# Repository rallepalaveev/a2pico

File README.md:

# A2Pico Reference Hardware

This repository is the home of the A2Pico reference hardware. Please refer to the upstream repository at https://github.com/oliverschmidt/a2pico for general information on A2Pico.

## Hardware Revision History

Version 1.4 is the innitial design with 3x 74LVC245 and 1x 74HC08 to prove the concept. However it is obsolete as it does not switch off the Expansion ROM ($C800-$CFFF), which is always available and could cause data bus conlisions if used with other cards that use this memory space.

Version 1.5 switches off the Expansion ROM ($C800-$CFFF) when $CFFF is accessed or when reset is issued, and switches it back on again when the slot memory is accessed (IOSelect).

Version 1.6 combines 3 of the logic chips into a PLD. 74LS08, 74LS133 and 74LS02 are replaced by ATF22V10.

The RPI usage is as follows:

| GPIO    | Usage     |
|:--------|:----------|
| 0       |  UART TX  |
| 1       |  UART RX  |
| 2 - 13  | A0 - A11  |
| 14      | R/W       |
| 15 - 22 | D0 - D7   |
| 26      | ENBL      |
| 27      | IRQ       |
| 28      | RES       |

Version "n" has support for a MicroSD card with **no** ExtROM capability.

The RPI usage of the "n" versions is as follows:

| GPIO    | Usage     |
|:--------|:----------|
| 0       |  SPI RX   |
| 1       |  SPI CSn  |
| 2       |  SPI SCK  |
| 3       |  SPI TX   |
| 4       |  NMI      |
| 5 - 12  | A0 - A7   |
| 13      | DEVSEL    |
| 14      | R/W       |
| 15 - 22 | D0 - D7   |
| 26      | ENBL      |
| 27      |  IRQ      |
| 28      |  RES      |

Version 1.7 is a direct successor of v1.4. Changes are replacing the 7408 by a 7411, data direction is controlled now by the Raspberry Pi Pico, which allows for all memory locations to be emulated, ENBL has an option to be is driven by a voltage divider for minimum latency, a USB "back power" option is included.

The RPI usage is as follows:

| GPIO    | Usage     |
|:--------|:----------|
| 0       |  UART TX  |
| 1       |  DATA dir |
| 2 - 13  | A0 - A11  |
| 14      | R/W       |
| 15 - 22 | D0 - D7   |
| 26      | ENBL      |
| 27      | IRQ       |
| 28      | RES       |

Versions 2.4 and 2.5 are a new hardware variant of v1.7 - TH and SMD respectively. The major change is that A0-7 and D0-7 are multiplexed and an SD card interface is added.
The RPI usage is as follows:

| GPIO    | Usage     |
|:--------|:----------|
| 0       |  UART Tx  |
| 1       |  UART Rx  |
| 2       |  ENBL     |
| 3 - 10  | AD0 - AD7 |
| 11 - 14 | A8 - A11  |
| 15      | R/W       |
| 16      | PHI1      |
| 17      | RES       |
| 18      | IRQ       |
| 19      | CMD       |
| 20      | DAT0      |
| 21      | DAT3      |
| 22      | CLK       |
| 26      | AL-OE     |
| 27      | D-OE      |
| 28      | DDIR      |

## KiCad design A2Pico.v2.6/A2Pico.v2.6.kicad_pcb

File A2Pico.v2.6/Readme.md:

A2Pico Version 2.6 is a follow-up of 2.4 with some small changes - changed form factor, added USB power slide switch, added USB power LED.

The RPI usage is as follows:

| GPIO    | Usage     |
|:--------|:----------|
| 0       |  UART Tx  |
| 1       |  UART Rx  |
| 2       |  ENBL     |
| 3 - 10  | AD0 - AD7 |
| 11 - 14 | A8 - A11  |
| 15      | R/W       |
| 16      | Ф1        |
| 17      | RES       |
| 18      | IRQ       |
| 19      | CMD       |
| 20      | DAT0      |
| 21      | DAT3      |
| 22      | CLK       |
| 26      | AL-OE     |
| 27      | D-OE      |
| 28      | DDIR      |

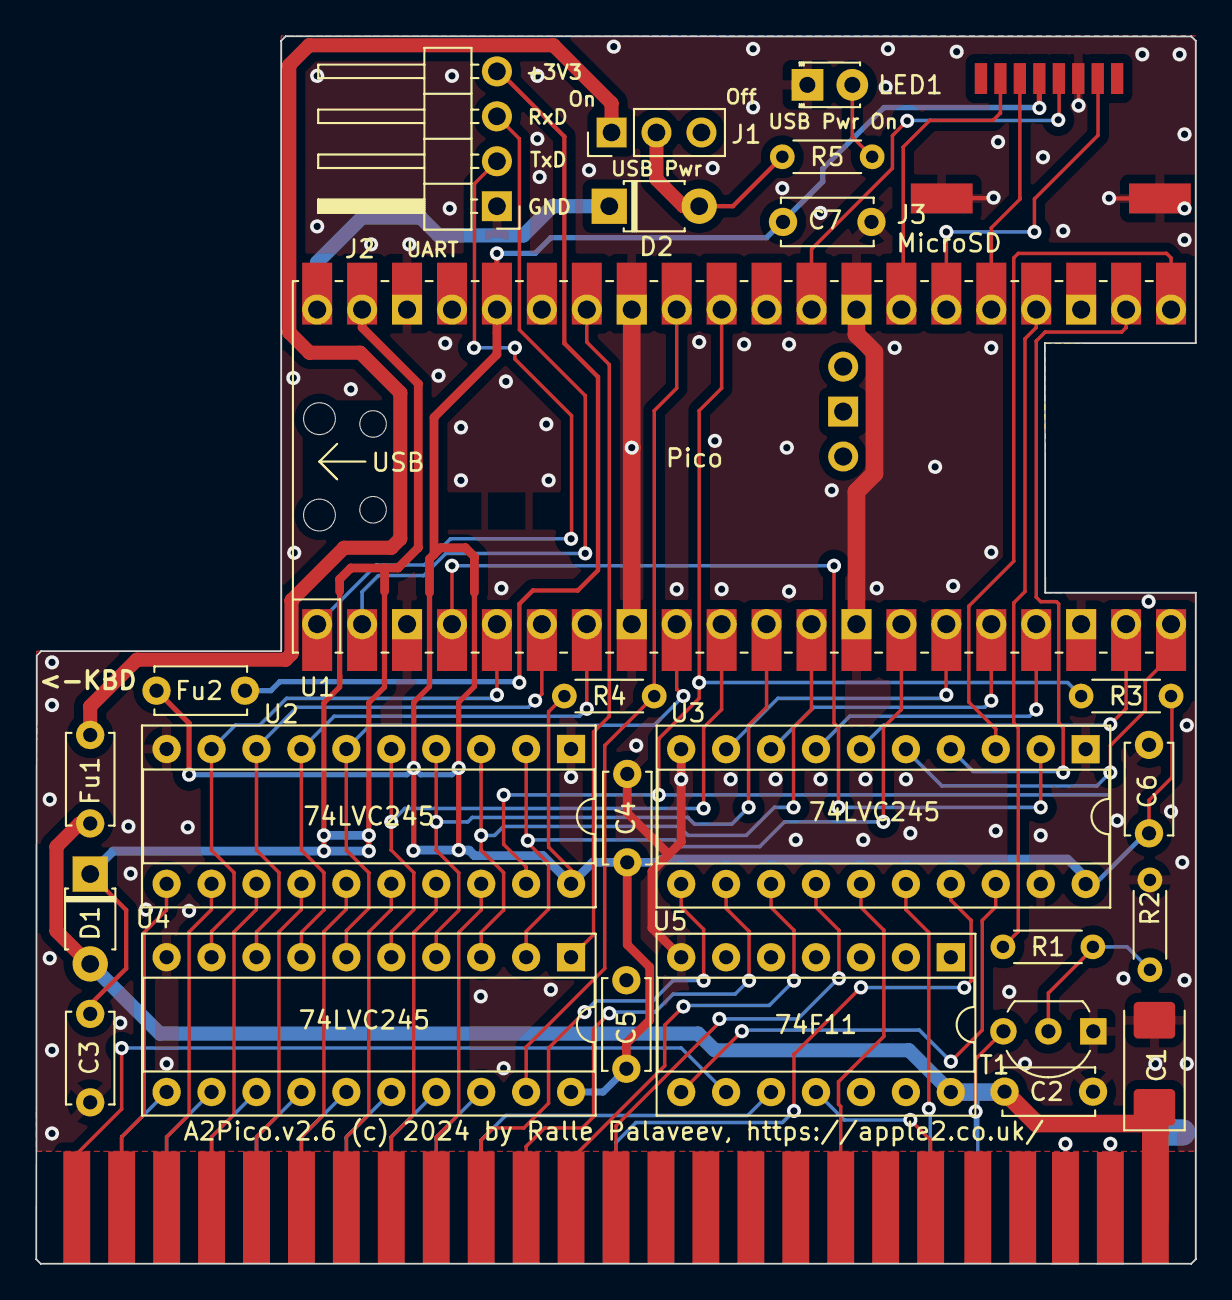
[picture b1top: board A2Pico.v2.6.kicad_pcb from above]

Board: 2 copper layers, 65.5 x 69.4 mm, 25 parts (0 on the bottom side), 31 nets.

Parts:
C1: 220uF; CP_EIA-6032-15_Kemet-U
C2, C3, C4, C5, C6, C7: 100n; C_Disc_D5.0mm_W2.5mm_P5.00mm
D1, D2: D_T-1_P5.08mm_Horizontal
Fu1: 500mA; C_Disc_D5.0mm_W2.5mm_P5.00mm
Fu2: 100mA; C_Disc_D5.0mm_W2.5mm_P5.00mm
J1: PinHeader_1x03_P2.54mm_Vertical
J2: PinHeader_1x04_P2.54mm_Horizontal
LED1: LED_D1.8mm_W3.3mm_H2.4mm
R1, R5: 1k; R_Axial_DIN0204_L3.6mm_D1.6mm_P5.08mm_Horizontal
R2, R3, R4: 10k; R_Axial_DIN0204_L3.6mm_D1.6mm_P5.08mm_Horizontal
T1: TO-92L_Inline_Wide
U1: Pico / PicoW; RPi_PicoW_SMD_TH
U2, U3, U4: 74LVC245; DIP-20_W7.62mm_Socket
U5: 74F11; DIP-14_W7.62mm_Socket

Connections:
3.3V: C4.1, C5.1, C6.1, C7.1, Fu2.1, R3.1, R4.2, U1.36 (3V3), U2.20, U3.20, U4.20
3.3V_out: Fu2.2, J2.4
5V: C1.1, C2.2, D1.2, Fu1.1, U5.14
AL-OE: R3.2, U1.31 (GPIO26_ADC0), U2.19
D-Dir: U1.34 (GPIO28_ADC2), U4.1
D-OE: R4.1, U1.32 (GPIO27_ADC1), U4.19
ENBL: U3.18, U5.8
GND: C1.2, C2.1, C3.1, C4.2, C5.2, C6.2, C7.2, J2.1, LED1.1, R2.2, T1.1, U1.3 (GND), U1.8 (GND), U1.13 (GND), U1.18 (GND), U1.23 (GND), U1.28 (GND), U1.33 (AGND), U1.38 (GND), U2.1, U2.10, U3.1, U3.10, U3.19, U4.10, U5.7
J1-1: Fu1.2, J1.1
J1-2: D2.2, J1.2, R5.2
L-A8: U1.15 (GPIO11), U3.9
L-A9: U1.16 (GPIO12), U3.8
L-A10: U1.17 (GPIO13), U3.7
L-A11: U1.19 (GPIO14), U3.6
L-AD0: U1.5 (GPIO3), U2.9, U4.9
L-AD1: U1.6 (GPIO4), U2.8, U4.8
L-AD2: U1.7 (GPIO5), U2.7, U4.7
L-AD3: U1.9 (GPIO6), U2.6, U4.6
L-AD4: U1.10 (GPIO7), U2.5, U4.5
L-AD5: U1.11 (GPIO8), U2.4, U4.4
L-AD6: U1.12 (GPIO9), U2.3, U4.3
L-AD7: U1.14 (GPIO10), U2.2, U4.2
L-ENBL: U1.4 (GPIO2), U3.2
L-IRQ: R1.2, U1.24 (GPIO18)
L-PHI1: U1.21 (GPIO16), U3.3
L-RW: U1.20 (GPIO15), U3.5
L-Reset: U1.22 (GPIO17), U3.4
Rx: J2.3, U1.2 (GPIO1)
Tx: J2.2, U1.1 (GPIO0)
VBUS: D2.1, U1.40 (VBUS)
VSYS: C3.2, D1.1, U1.39 (VSYS)

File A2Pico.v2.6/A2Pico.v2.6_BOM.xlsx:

Comment | Designator
10V 100uF | C1
16V 100nF | C2,C3,C4,C5,C6,C7,C8
1K | R1,R5
10K | R2,R3,R4
MicroSD slot without cover, Attend 112K-TAA0-RA1 | J3
Slide switch CUI Devices MSS-102568-14A-90-D | J1
3A Right-Angle Square Pins 2.5mm 4P 6mm | J2
6V 500mA Resettable Fuse | Fu1
6V 100mA Resettable Fuse | Fu2
1N5819 | D1,D2
2N7002 | T1
Raspberry Pi PICO | U1
SN74LVC245N | U2,U3,U4
74F11 | U5
LED | LED1

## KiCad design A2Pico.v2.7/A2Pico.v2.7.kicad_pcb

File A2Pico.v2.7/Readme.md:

A2Pico Version 2.7 is a follow-up of 2.5 with some small changes - changed form factor, added USB power slide switch, added USB power LED.

The RPI usage is as follows:

| GPIO    | Usage     |
|:--------|:----------|
| 0       |  UART Tx  |
| 1       |  UART Rx  |
| 2       |  ENBL     |
| 3 - 10  | AD0 - AD7 |
| 11 - 14 | A8 - A11  |
| 15      | R/W       |
| 16      | Ф1        |
| 17      | RES       |
| 18      | IRQ       |
| 19      | CMD       |
| 20      | DAT0      |
| 21      | DAT3      |
| 22      | CLK       |
| 26      | AL-OE     |
| 27      | D-OE      |
| 28      | DDIR      |

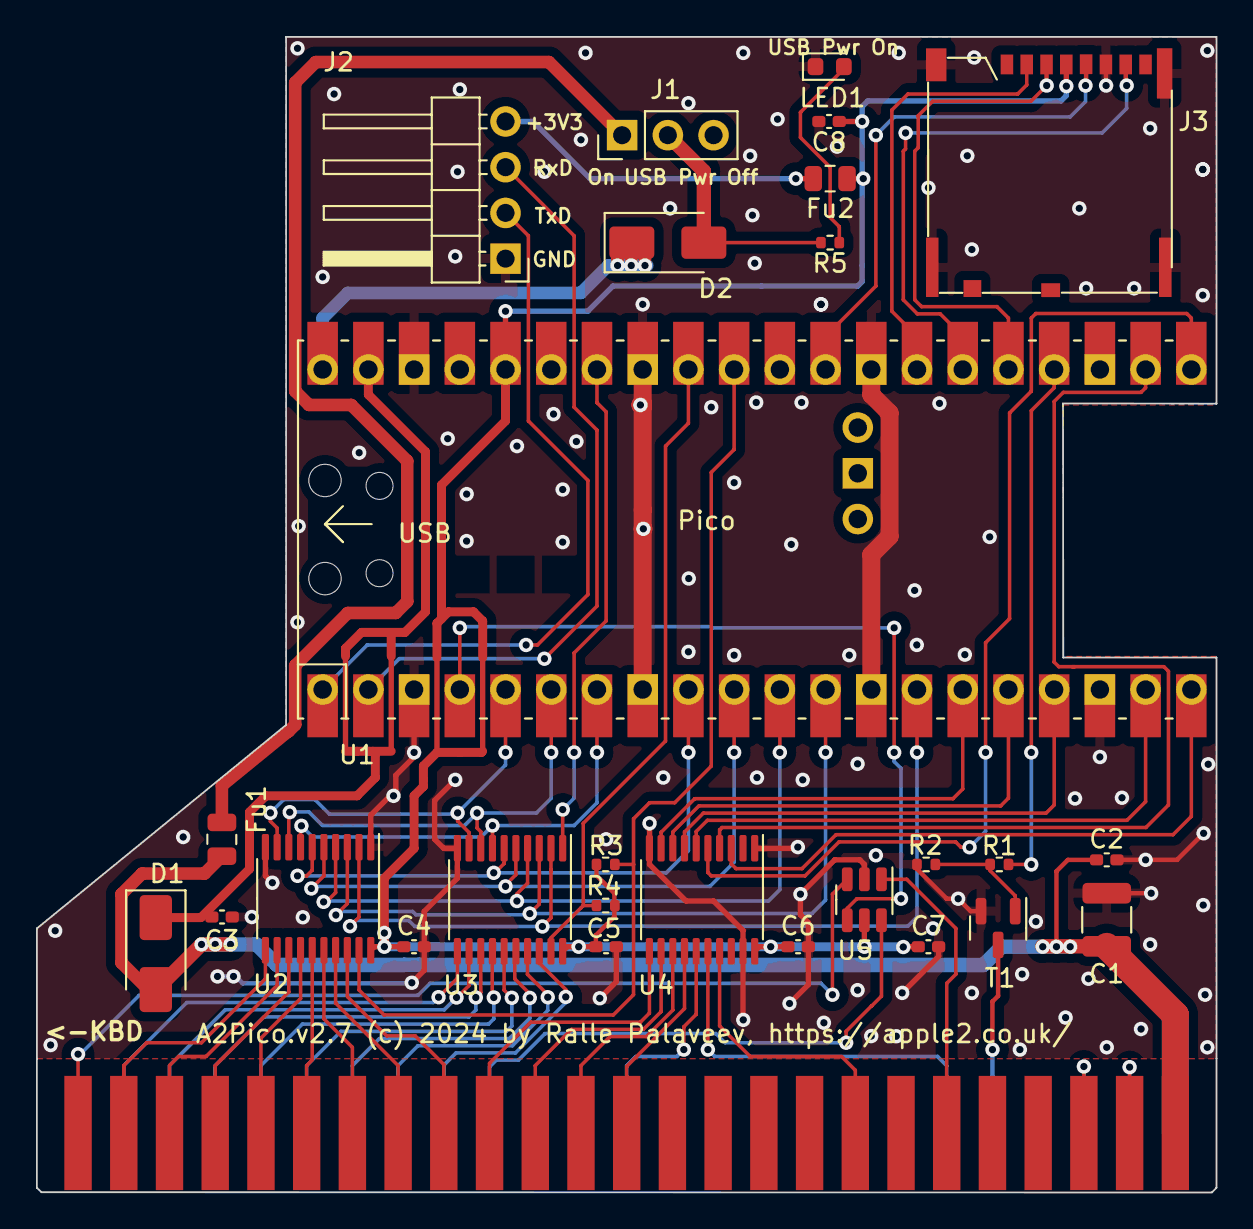
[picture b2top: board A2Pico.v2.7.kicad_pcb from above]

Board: 2 copper layers, 65.5 x 64.2 mm, 27 parts (0 on the bottom side), 35 nets.

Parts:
C1: C_1210_3225Metric
C2, C3, C4, C5, C6, C7, C8: 100n; C_0402_1005Metric_Pad0.74x0.62mm_HandSolder
D1, D2: SS16; D_SMA
Fu1, Fu2: Fuse_0805_2012Metric
J1: PinHeader_1x03_P2.54mm_Vertical
J2: PinHeader_1x04_P2.54mm_Horizontal
J3: microSD_HC_Molex_104031-0811
LED1: LED_0603_1608Metric
R1, R5: 1k; R_0402_1005Metric
R2, R3, R4: 10k; R_0402_1005Metric
T1: BS170F-BV; SOT-23
U1: Pico; RPi_PicoW_SMD_TH
U2, U3, U4: SN74LVC245APWR; TSSOP-20_4.4x6.5mm_P0.65mm
U5: SN74LVC1G11DBVR; SOT-23-6

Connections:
3.3V: C4.1, C5.1, C6.1, C7.1, C8.2, Fu2.1, J3.4, R3.2, R4.1, U1.36 (3V3), U2.20, U3.20, U4.20, U5.5
3.3V_out: Fu2.2, J2.4
5V: C1.1, C2.1, D1.2, Fu1.2
AL-OE: R3.1, U1.31 (GPIO26_ADC0), U2.19
CLK: J3.5, U1.29 (GPIO22)
CMD: J3.3, U1.25 (GPIO19)
D-Dir: U1.34 (GPIO28_ADC2), U3.1
D-OE: R4.2, U1.32 (GPIO27_ADC1), U3.19
DAT0: J3.7, U1.26 (GPIO20)
DAT3: J3.2, U1.27 (GPIO21)
ENBL: U1.4 (GPIO2), U5.4
GND: C1.2, C2.2, C3.2, C4.2, C5.2, C6.2, C7.2, C8.1, J2.1, J3.6, J3.11, LED1.1, R2.2, T1.2, U1.3 (GND), U1.8 (GND), U1.13 (GND), U1.18 (GND), U1.23 (GND), U1.28 (GND), U1.33 (AGND), U1.38 (GND), U2.1, U2.10, U3.10, U4.1, U4.10, U4.19, U5.2
J1-1: Fu1.1, J1.1
J1-2: D2.2, J1.2, R5.2
L-A8: U1.15 (GPIO11), U4.9
L-A9: U1.16 (GPIO12), U4.8
L-A10: U1.17 (GPIO13), U4.7
L-A11: U1.19 (GPIO14), U4.6
L-AD0: U1.5 (GPIO3), U2.9, U3.9
L-AD1: U1.6 (GPIO4), U2.8, U3.8
L-AD2: U1.7 (GPIO5), U2.7, U3.7
L-AD3: U1.9 (GPIO6), U2.6, U3.6
L-AD4: U1.10 (GPIO7), U2.5, U3.5
L-AD5: U1.11 (GPIO8), U2.4, U3.4
L-AD6: U1.12 (GPIO9), U2.3, U3.3
L-AD7: U1.14 (GPIO10), U2.2, U3.2
L-IRQ: R1.1, U1.24 (GPIO18)
L-PHI: U1.21 (GPIO16), U4.5
L-RW: U1.20 (GPIO15), U4.3
L-Reset: U1.22 (GPIO17), U4.4
Rx: J2.3, U1.2 (GPIO1)
Tx: J2.2, U1.1 (GPIO0)
VBUS: D2.1, U1.40 (VBUS)
VSYS: C3.1, D1.1, U1.39 (VSYS)
m-IRQ: R1.2, R2.1, T1.1

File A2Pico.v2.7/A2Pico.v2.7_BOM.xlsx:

Comment | Designator | Footprint | JLCPCB Part #（optional）
10V 100uF X5R ±20% 1210 Multilayer Ceramic Capacitors MLCC - SMD/SMT ROHS | C1 | 1210 | C386065
16V 100nF X7R ±10% 0402 Multilayer Ceramic Capacitors MLCC - SMD/SMT ROHS | C2,C3,C4,C5,C6,C7,C8 | 0402 | C1525
1K | R1,R5 | 0402 | C11702
10K | R2,R3,R4 | 0402 | C25744
1.28mm Gold Deck MicroSD card (TF card) Self bomb SMD SD Card Connectors ROHS | J3 | SMD | C428492
3A Straight Square Pins 2.54mm 6mm -40℃~+105℃ 1 2 3mm 2.54mm Blac | J1 | PinHeader_1x02_P2.54mm_Vertical | C492401
3A Right-Angle Square Pins 2.5mm 4P 6mm | J2 | PinHeader_1x04_P2.54mm_Vertical | C2829875
6V 500mA Resettable Fuse | Fu1 | 0805-50 | C782729
6V 100mA Resettable Fuse | Fu2 | 0805 | C20975
SS16 SBD | D1,D2 | SMA(DO-214AC) | C908233
BS170F-BV | T1 | SOT-23 | C558098
Raspberry Pi PICO | U1 |  | C7203002
SN74LVC245APWR | U2,U3,U4 | TSSOP-20 | C7848
SN74LVC1G11DBVR | U5 | SOT-23-6 | C22046
White LED | LED1 | 0402 | C6848499

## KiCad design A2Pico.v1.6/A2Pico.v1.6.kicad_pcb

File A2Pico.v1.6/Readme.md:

Version 1.6 combines 3 of the logic chips into a PLD.
74LS08, 74LS133 and 74LS02 are replaced by ATF22V10.

The RPI usage is as follows:

| GPIO    | Usage     |
|:--------|:----------|
| 0       |  UART TX  |
| 1       |  UART RX  |
| 2 - 13  | A0 - A11  |
| 14      | R/W       |
| 15 - 22 | D0 - D7   |
| 26      | ENBL      |
| 27      | IRQ       |
| 28      | RES       |

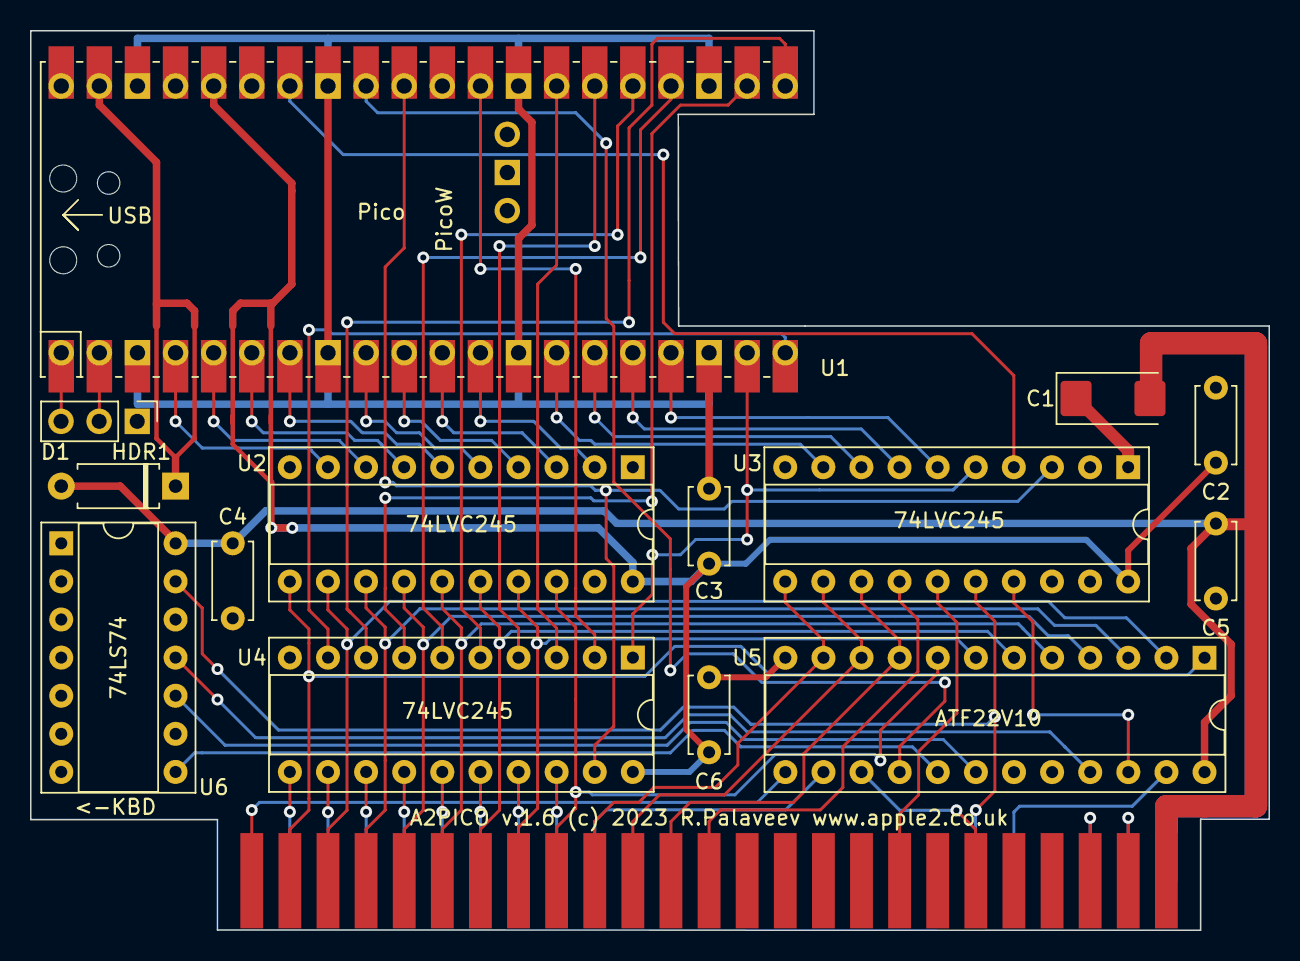
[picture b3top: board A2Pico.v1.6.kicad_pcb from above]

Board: 2 copper layers, 82.5 x 60.0 mm, 14 parts (0 on the bottom side), 4 nets.

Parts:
C1: 220uF; CP_EIA-6032-15_Kemet-U
C2, C3, C4, C5, C6: 100n; C_Disc_D5.0mm_W2.5mm_P5.00mm
D1: D_A-405_P7.62mm_Horizontal
HDR1: PinHeader_1x03_P2.54mm_Vertical
U1: PicoW; RPi_PicoW_SMD_TH
U2, U3, U4: 74LVC245; DIP-20_W7.62mm_Socket
U5: ATF22V10; DIP-24_W7.62mm_Socket
U6: 74LS74; DIP-14_W7.62mm_Socket

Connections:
3.3V: C2.1, C3.1, C6.1, U1.36 (3V3), U2.20, U3.20, U4.20
5V: C1.2, C4.2, C5.2, D1.2, U5.24, U6.14
GND: C1.1, C2.2, C3.2, C4.1, C5.1, C6.2, HDR1.1, U1.3 (GND), U1.8 (GND), U1.13 (GND), U1.18 (GND), U1.23 (GND), U1.28 (GND), U1.33 (AGND), U1.38 (GND), U2.1, U2.10, U2.19, U3.1, U3.10, U3.19, U4.10, U5.12, U6.2, U6.7, U6.12
VSYS: D1.1, U1.39 (VSYS)

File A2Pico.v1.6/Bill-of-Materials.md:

|Qty|Designator|Item|Package|Description|
|---|---|---|---|---|
|1x|C1|6.3V 220uF X5R|0805|Multilayer Ceramic Capacitor|
|5x|C2-C6|50V 100nF X7R|0402|Multilayer Ceramic Capacitor|
|1x|D1|SS14F|SMAF|40V 550mV @ 1A Shottkey Barrier Diode|
|1x|U1|Pico-W|Module|Raspberry Pi Pico or Pico-W module (no pins)|
|3x|U2-U4|SN74LVC245A|PDIP-20|Texas Instruments SN74LVC245A Octal Bus Transceiver With 3-State Outputs|
|1x|U5|ATF22V10C-10PC|PDIP-24|Microchip ATF22V10C PLD|
|1x|U6|SN74LS74|PDIP-14|Dual Positive-Edge-Triggered D Flip-Flops with Pr, Cl and Complementary Outputs|
|1x|HDR1|3-pin Header|HD-3|TH PinHeader_1x03_P2.54mm_Vertical|

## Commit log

2023-12-18 Rename README.md to README.md
2023-12-18 Rename CMakeLists.txt to CMakeLists.txt
2023-12-18 Rename pico_sdk_import.cmake to pico_sdk_import.cmake
2023-12-18 Rename board.c to board.c
2023-12-18 Rename board.h to board.h
2023-12-18 Rename main.c to main.c
2023-12-18 Rename bus.pio to bus.pio
2023-12-18 Rename firmware.S to firmware.S
2023-12-18 Rename firmware.cfg to firmware.cfg
2023-12-18 Rename incbin.S to incbin.S
2023-12-18 Add demo for v1.7
2023-12-30 Rename LICENSE.md to LICENSE.md
2023-12-30 Rename A2PICO.v1.7.sch.pdf to A2Pico.v1.7.sch.pdf
2023-12-30 Rename A2PICO-n.v1.6-gerbers.rar to A2Pico-n.v1.6-gerbers.rar
2023-12-30 Rename A2PICO-n.v1.6.jpg to A2Pico-n.v1.6.jpg
2023-12-30 Rename A2PICO-n.v1.6_sch.pdf to A2Pico-n.v1.6_sch.pdf
2023-12-30 Rename
2024-03-07 Rename A2Pico.v2.5.png to A2Pico.v2.5-render.png
2024-03-07 Rename A2Pico.v2.5-render.png to A2Pico.v2.5.render.png
2024-03-07 Rename A2Pico.v2.5.pdf to A2Pico.v2.5.pic.pdf
2024-03-07 Rename A2Pico.v2.4.png to A2Pico.v2.4.render.png
2024-03-07 Rename A2Pico.v2.4.pdf to A2Pico.v2.4.pic.pdf
2024-03-11 Rename A2Pico.v2.4-gerbers.rar to A2Pico.v2.4.gerbers.rar
2024-03-11 Rename A2Pico.v2.5-design-files.rar to A2Pico.v2.5.design.files.rar
2024-03-14 Rename A2Pico.v2.7-web.png to A2Pico.v2.7.png
2024-07-13 Clarify roles of the different repos.

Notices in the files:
A2Pico.v1.6/A2Pico.v1.6.kicad_pcb:
A2PICO v.1.6 (c) 2023 R.Palaveev www.apple2.co.uk
A2Pico.v2.6/A2Pico.v2.6.kicad_pcb:
A2Pico v2.6 (c) 2024
A2Pico.v2.6 (c) 2024 by Ralle Palaveev, https://apple2.co.uk
A2Pico.v2.7/A2Pico.v2.7.kicad_pcb:
A2Pico v2.7 (c) 2024
A2Pico.v2.7 (c) 2024 by Ralle Palaveev, https://apple2.co.uk
